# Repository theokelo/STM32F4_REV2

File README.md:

# STM32F4_REV2
STM3F4 Board based on Phil's Lab's "Little Brain"

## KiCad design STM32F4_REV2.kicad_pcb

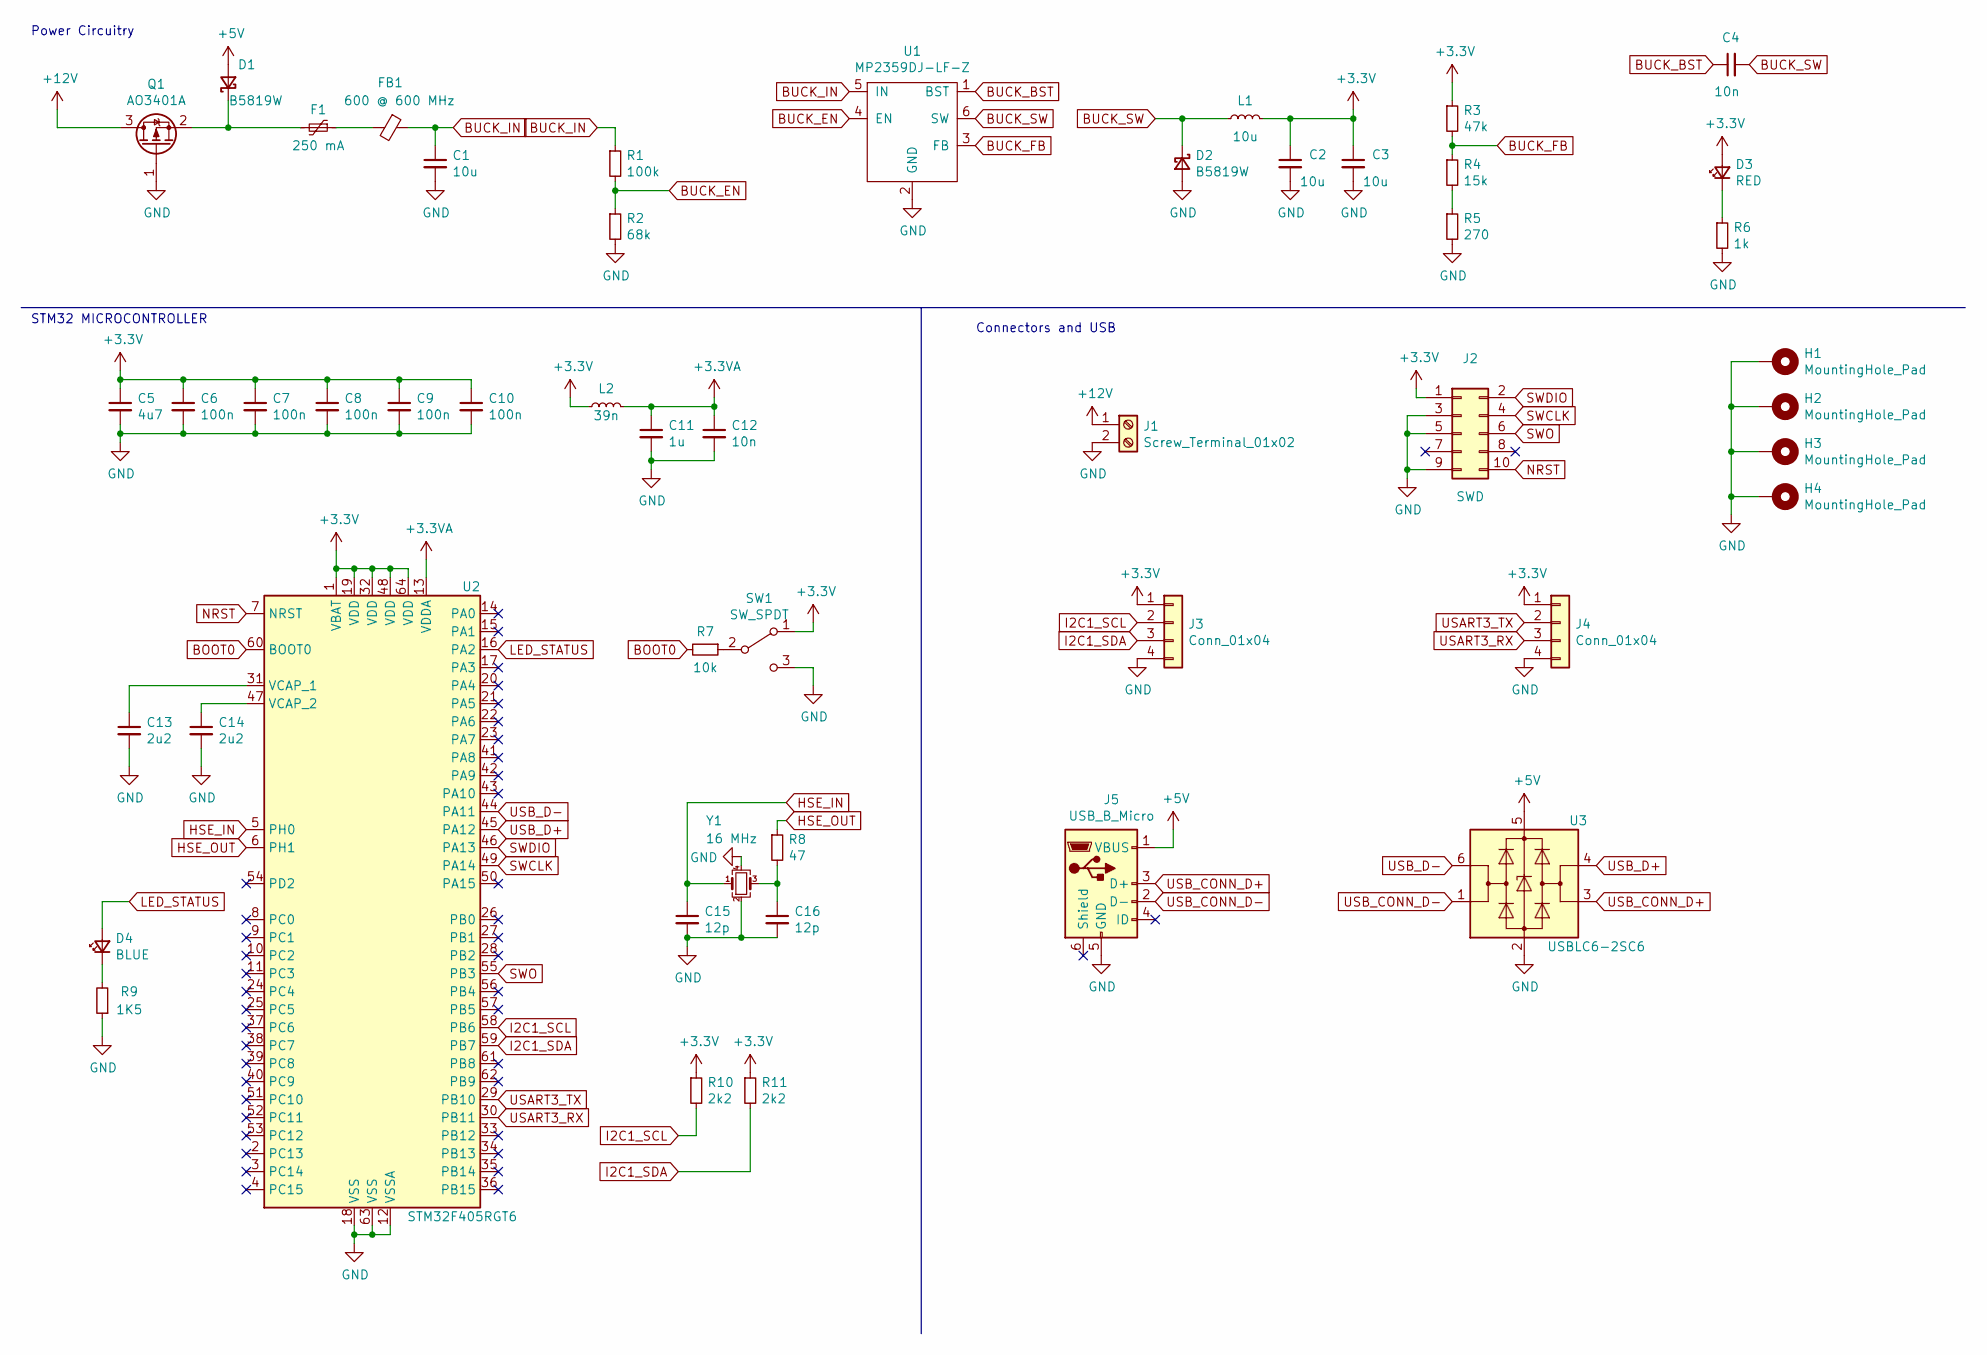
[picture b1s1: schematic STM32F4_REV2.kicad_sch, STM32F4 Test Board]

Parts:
C1, C2, C3: 10u; C_1206_3216Metric
C4: 10n; C_0603_1608Metric
C5: 4u7; C_0603_1608Metric
C6, C7, C8, C9, C10: 100n; C_0402_1005Metric
C11: 1u; C_0402_1005Metric
C12: 10n; C_0402_1005Metric
C13, C14: 2u2; C_0603_1608Metric
C15, C16: 12p; C_0402_1005Metric
D1, D2: B5819W; D_SOD-123
D3: RED; LED_0603_1608Metric
D4: BLUE; LED_0603_1608Metric
F1: 250 mA; Fuse_1206_3216Metric
FB1: 600 @ 600 MHz; L_0805_2012Metric
H1, H2, H3, H4: MountingHole_Pad; MountingHole_4.3mm_M4_Pad_Via
J1: Screw_Terminal_01x02; TerminalBlock_Phoenix_PT-1,5-2-3.5-H_1x02_P3.50mm_Horizontal
J2: SWD; PinSocket_2x05_P1.27mm_Vertical_SMD
J3, J4: Conn_01x04; Molex_PicoBlade_53048-0410_1x04_P1.25mm_Horizontal
J5: USB_B_Micro; USB_Micro-B_GCT_USB3076-30-A
L1: 10u; L_Sunlord_MWSA0518_5.4x5.2mm
L2: 39n; L_0402_1005Metric
Q1: AO3401A; SOT-23
R1: 100k; R_0603_1608Metric
R2: 68k; R_0603_1608Metric
R3: 47k; R_0603_1608Metric
R4: 15k; R_0603_1608Metric
R5: 270; R_0603_1608Metric
R6: 1k; R_0603_1608Metric
R7: 10k; R_0402_1005Metric
R8: 47; R_0402_1005Metric
R9: 1K5; R_0603_1608Metric
R10, R11: 2k2; R_0402_1005Metric
SW1: SW_SPDT; SW_SPDT_PCM12
U1: MP2359DJ-LF-Z; SOT-23-6
U2: STM32F405RGT6; LQFP-64_10x10mm_P0.5mm
U3: USBLC6-2SC6; SOT-23-6
Y1: 16 MHz; Crystal_SMD_3225-4Pin_3.2x2.5mm

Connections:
+3.3VA: C11.1, C12.1, L2.2, U2.13 (VDDA)
+3V3: C2.1, C3.1, C5.1, C6.1, C7.1, C8.1, C9.1, C10.1, D3.2 (A), J2.1, J3.1, J4.1, L1.2, L2.1, R3.1, R10.1, R11.1, SW1.1 (A), U2.1 (VBAT), U2.19 (VDD), U2.32 (VDD), U2.48 (VDD), U2.64 (VDD)
+5V: D1.2 (A), J5.1 (VBUS), U3.5 (VBUS)
+12V: J1.1, Q1.3 (D)
BOOT0: R7.2, U2.60 (BOOT0)
BUCK_BST: C4.1, U1.1 (BST)
BUCK_EN: R1.2, R2.1, U1.4 (EN)
BUCK_FB: R3.2, R4.1, U1.3 (FB)
BUCK_IN: C1.1, FB1.1, R1.1, U1.5 (IN)
BUCK_SW: C4.2, D2.1 (K), L1.1, U1.6 (SW)
GND: C1.2, C2.2, C3.2, C5.2, C6.2, C7.2, C8.2, C9.2, C10.2, C11.2, C12.2, C13.2, C14.2, C15.2, C16.2, D2.2 (A), H1.1, H2.1, H3.1, H4.1, J1.2, J2.3, J2.5, J2.9, J3.4, J4.4, J5.5 (GND), Q1.1 (G), R2.2, R5.2, R6.2, R9.1, SW1.3 (C), U1.2 (GND), U2.12 (VSSA), U2.18 (VSS), U2.63 (VSS), U3.2 (GND), Y1.2, Y1.4
HSE_IN: C15.1, U2.5 (PH0), Y1.1
HSE_OUT: R8.1, U2.6 (PH1)
I2C1_SCL: J3.2, R10.2, U2.58 (PB6)
I2C1_SDA: J3.3, R11.2, U2.59 (PB7)
LED_STATUS: D4.2 (A), U2.16 (PA2)
NRST: J2.10, U2.7 (NRST)
unnamed: C13.1, U2.31 (VCAP_1)
unnamed: C14.1, U2.47 (VCAP_2)
unnamed: C16.1, R8.2, Y1.3
unnamed: D1.1 (K), F1.2, Q1.2 (S)
unnamed: D3.1 (K), R6.1
unnamed: D4.1 (K), R9.2
unnamed: F1.1, FB1.2
unnamed: R4.2, R5.1
unnamed: R7.1, SW1.2 (B)
SWCLK: J2.4, U2.49 (PA14)
SWDIO: J2.2, U2.46 (PA13)
SWO: J2.6, U2.55 (PB3)
USART3_RX: J4.3, U2.30 (PB11)
USART3_TX: J4.2, U2.29 (PB10)
USB_CONN_D+: J5.3 (D+), U3.3 (I/O2)
USB_CONN_D-: J5.2 (D-), U3.1 (I/O1)
USB_D+: U2.45 (PA12), U3.4 (I/O2)
USB_D-: U2.44 (PA11), U3.6 (I/O1)

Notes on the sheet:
STM32 MICROCONTROLLER
Power Circuitry
Connectors and USB

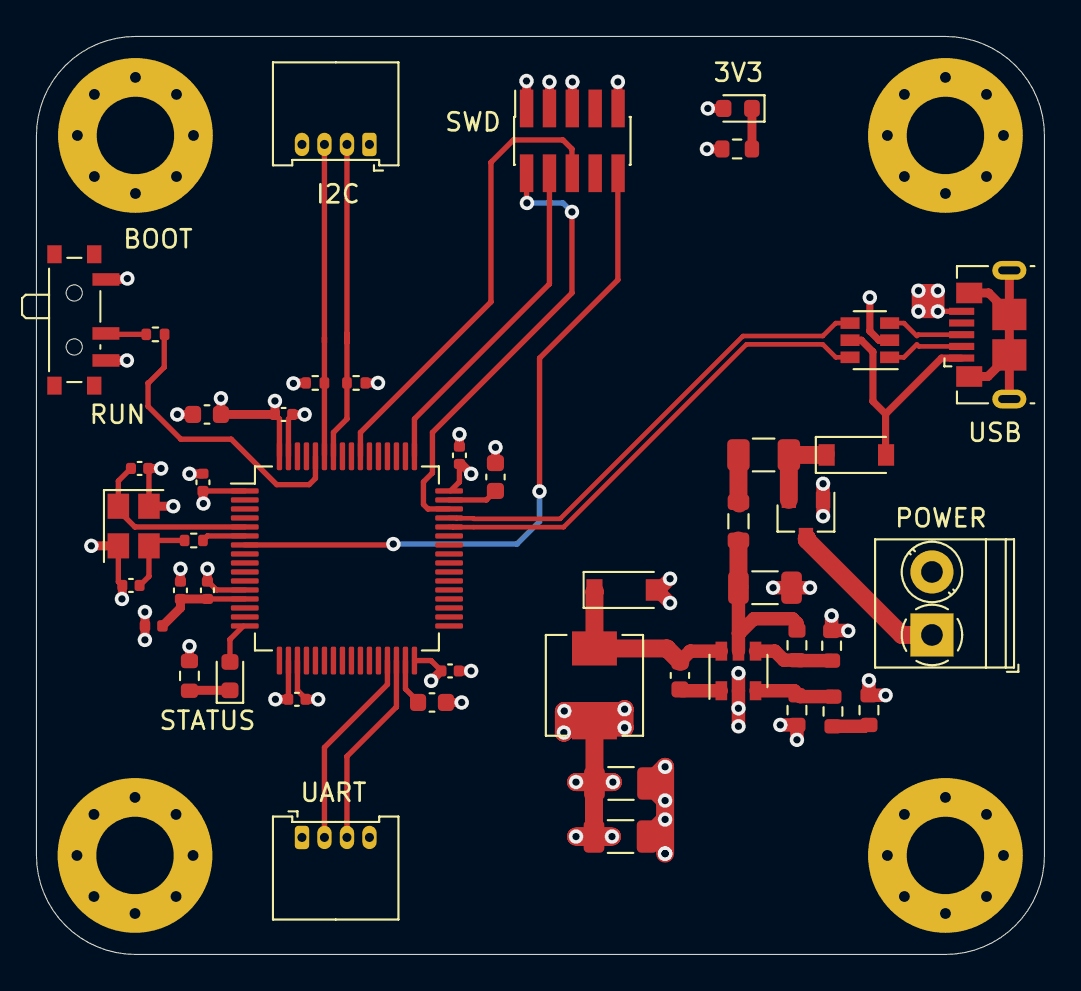
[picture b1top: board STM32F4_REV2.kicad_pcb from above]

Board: 4 copper layers, 56.0 x 51.0 mm, 50 parts (0 on the bottom side), 35 nets.
